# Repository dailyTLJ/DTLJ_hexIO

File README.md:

# DTLJ_hexIO

Custom circuit board to connect 16 units of an analog sensor and a LED. Control via a 16-channel Analog Multiplexer and a 16-channel Constant-Current LED driver (+ shifter register). The boards are chainable besides the analog output of the multiplexers. 

v1 has SOIC packages for the two chips, and through-hole packages for all other parts, for easier soldering. 

* 2-layer board
* 3.4 x 2.9 inches
* 35 mil power traces, 20 mil default traces
* 13 mil minimum drill size
* 10 mil clearance btw. traces

What it looks like assembled

## Things to change in next iteration

* indicator of LED polarity (on power LED, and sensor-module LEDs)
* analog output pin hole too big

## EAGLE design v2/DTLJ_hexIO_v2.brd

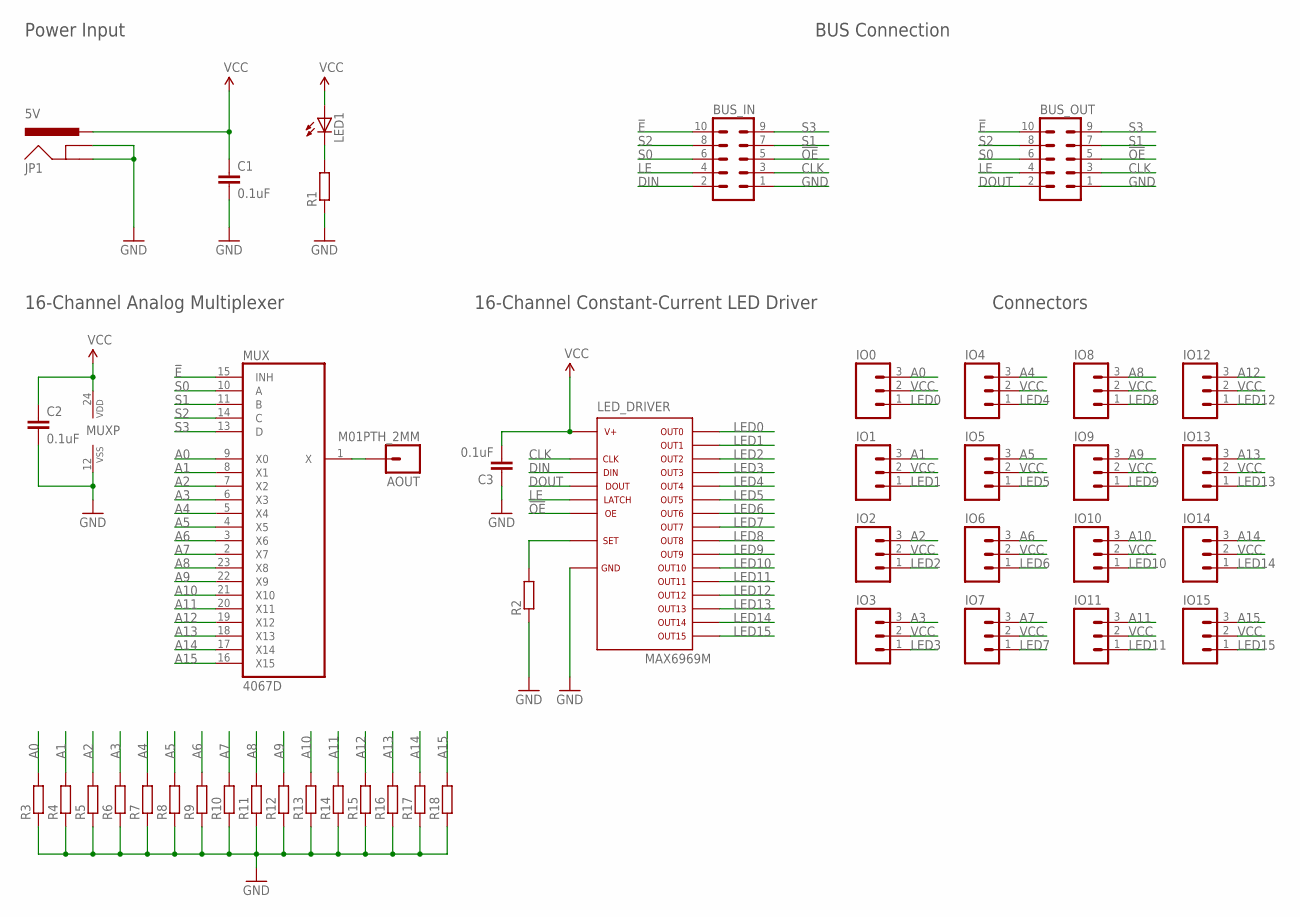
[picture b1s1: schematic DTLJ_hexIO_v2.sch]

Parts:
AOUT: M01PTH_2MM; 1X01_2MM
BUS_IN: ML10
BUS_OUT: ML10
C1, C2, C3: 0.1uF; C1206
IO0, IO1, IO2, IO3, IO4, IO5, IO6, IO7, IO8, IO9, IO10, IO11, IO12, IO13, IO14, IO15: M03POLAR; MOLEX-1X3
JP1: 5V; POWER_JACK_PTH_BREAD
LED1: LEDSMT1206; 1206
LED_DRIVER: MAX6969M; SO24W
MUX: 4067D; SO24W
R1, R2, R3, R4, R5, R6, R7, R8, R9, R10, R11, R12, R13, R14, R15, R16, R17, R18: R-EU_R1206; R1206

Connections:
!E: BUS_IN.10, BUS_OUT.10, MUX.15 (INH)
!OE: BUS_IN.5, BUS_OUT.5, LED_DRIVER.21
A0: IO0.3, MUX.9 (X0), R3.2
A1: IO1.3, MUX.8 (X1), R4.2
A2: IO2.3, MUX.7 (X2), R5.2
A3: IO3.3, MUX.6 (X3), R6.2
A4: IO4.3, MUX.5 (X4), R7.2
A5: IO5.3, MUX.4 (X5), R8.2
A6: IO6.3, MUX.3 (X6), R9.2
A7: IO7.3, MUX.2 (X7), R10.2
A8: IO8.3, MUX.23 (X8), R11.2
A9: IO9.3, MUX.22 (X9), R12.2
A10: IO10.3, MUX.21 (X10), R13.2
A11: IO11.3, MUX.20 (X11), R14.2
A12: IO12.3, MUX.19 (X12), R15.2
A13: IO13.3, MUX.18 (X13), R16.2
A14: IO14.3, MUX.17 (X14), R17.2
A15: IO15.3, MUX.16 (X15), R18.2
CLK: BUS_IN.3, BUS_OUT.3, LED_DRIVER.3
DIN: BUS_IN.2, LED_DRIVER.2
DOUT: BUS_OUT.2, LED_DRIVER.22
GND: BUS_IN.1, BUS_OUT.1, C1.2, C2.2, C3.1, JP1.GND, JP1.GNDBREAK, LED_DRIVER.1, MUX.12 (VSS), R1.1, R2.1, R3.1, R4.1, R5.1, R6.1, R7.1, R8.1, R9.1, R10.1, R11.1, R12.1, R13.1, R14.1, R15.1, R16.1, R17.1, R18.1
LE: BUS_IN.4, BUS_OUT.4, LED_DRIVER.4
LED0: IO0.1, LED_DRIVER.5
LED1: IO1.1, LED_DRIVER.6
LED2: IO2.1, LED_DRIVER.7
LED3: IO3.1, LED_DRIVER.8
LED4: IO4.1, LED_DRIVER.9
LED5: IO5.1, LED_DRIVER.10
LED6: IO6.1, LED_DRIVER.11
LED7: IO7.1, LED_DRIVER.12
LED8: IO8.1, LED_DRIVER.13
LED9: IO9.1, LED_DRIVER.14
LED10: IO10.1, LED_DRIVER.15
LED11: IO11.1, LED_DRIVER.16
LED12: IO12.1, LED_DRIVER.17
LED13: IO13.1, LED_DRIVER.18
LED14: IO14.1, LED_DRIVER.19
LED15: IO15.1, LED_DRIVER.20
unnamed: LED1.C, R1.2
unnamed: LED_DRIVER.23, R2.2
unnamed: AOUT.1, MUX.1 (X)
S0: BUS_IN.6, BUS_OUT.6, MUX.10 (A)
S1: BUS_IN.7, BUS_OUT.7, MUX.11 (B)
S2: BUS_IN.8, BUS_OUT.8, MUX.14 (C)
S3: BUS_IN.9, BUS_OUT.9, MUX.13 (D)
VCC: C1.1, C2.1, C3.2, IO0.2, IO1.2, IO2.2, IO3.2, IO4.2, IO5.2, IO6.2, IO7.2, IO8.2, IO9.2, IO10.2, IO11.2, IO12.2, IO13.2, IO14.2, IO15.2, JP1.PWR, LED1.A, LED_DRIVER.24, MUX.24 (VDD)

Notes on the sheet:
Power Input
BUS Connection
16-Channel Analog Multiplexer
16-Channel Constant-Current LED Driver
Connectors

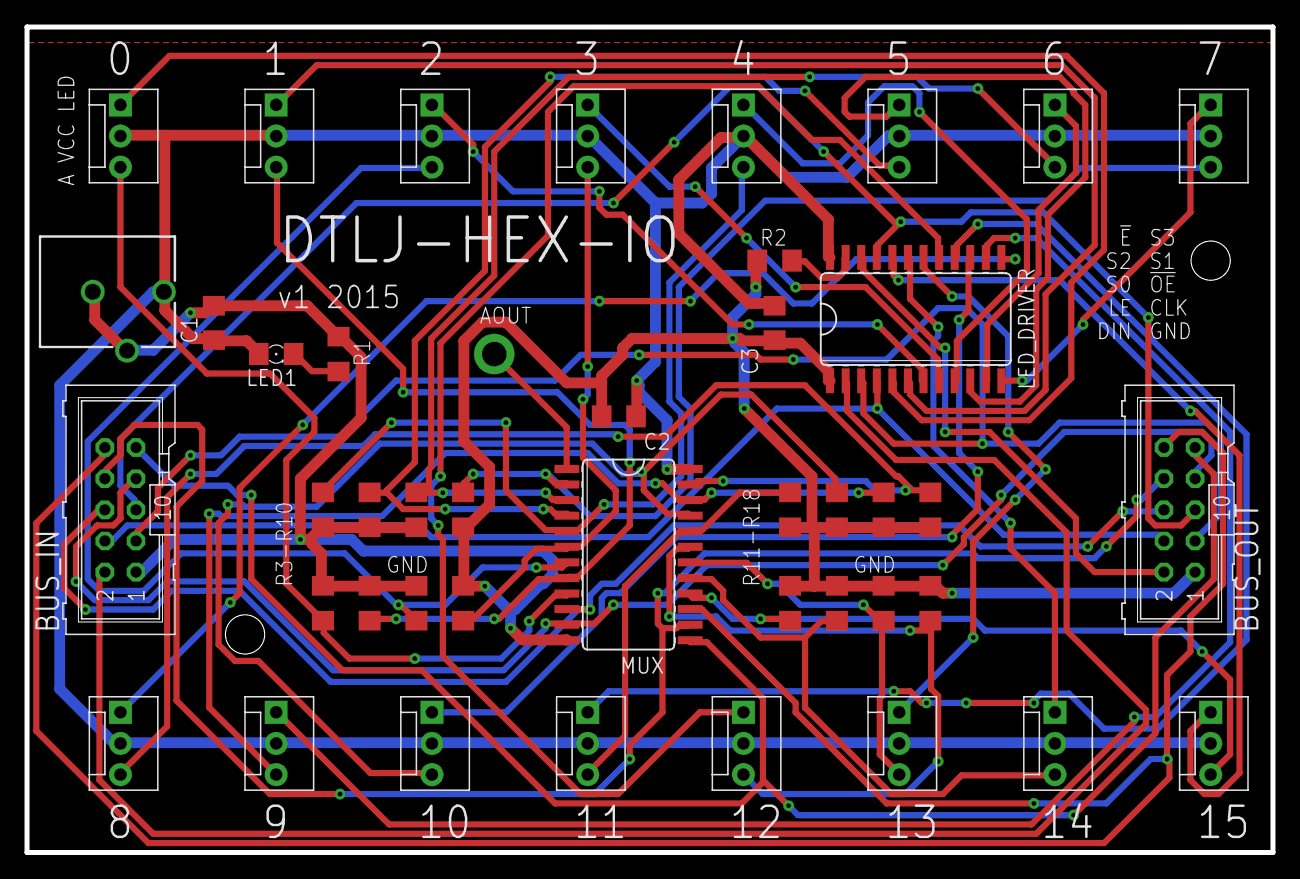
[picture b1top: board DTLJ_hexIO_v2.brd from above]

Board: 2 copper layers, 101.6 x 67.3 mm, 44 parts (0 on the bottom side), 47 nets.

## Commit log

2015-02-22 ready for a first round of Golden Phoenix
2015-02-23 v2 = smd version
2015-03-08 assembled pic

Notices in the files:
parts and their libraries:
SparkFun-Connectors: Licensing: Creative Commons ShareAlike 4.0 International - https://creativecommons.org/licenses/by-sa/4.0
